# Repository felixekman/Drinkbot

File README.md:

Drinkbot
========

An attempt at controlling a bunch of peristaltic pumps

I have ordered 8 Peristaltic Pumps. 12VDC 200-300mA
  https://www.adafruit.com/products/1150

I hope to drive them via a Raspberry Pi Model B and a Spark core.
I want to be able to control the pumps individually with Mosfets for ON/OFF operation (Possibly via PWM) from the GPIO pins on the Raspberry Pi. I hope to connect the pumps via RJ45 connectors for easy connect and disconnect. I want to drive the entire system from a single 12V power supply.
My current plan is to build my own PCB (first time ever so I need a little help) using these components and ordering the PCB from OSHPark.

Components for the build:

1 pcs Raspberry Pi Model B

1 pcs Spark Core http://spark.io

8 pcs Peristaltic Pumps. 12VDC 200-300mA (https://www.adafruit.com/products/1150)

8 pcs RJ45 8-Pin connectors (https://www.sparkfun.com/products/643)

8 pcs N-Channel MOSFET 60V 30A FQP30N06L (https://www.sparkfun.com/products/10213)

8 pcs 10k Ohm 1/4th W Resistors (https://www.sparkfun.com/products/8374)

8 pcs 1N4007 Diode MIC DO-41 1A 1000V Rectifier Diode

1 pcs Voltage Regulator - 5V L7805 (https://www.sparkfun.com/products/107)

1 pcs Raspberry Pi - GPIO Shrouded Header (2x13)

This project is released under Open Source Hardware (OSHW) licence and the coming software is released under a OSI-approved open source license!

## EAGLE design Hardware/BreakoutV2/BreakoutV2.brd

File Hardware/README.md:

Drinkbot
========

Version 1 of Drinkbot Hardware
Schematics and Layout in Eagle CAD

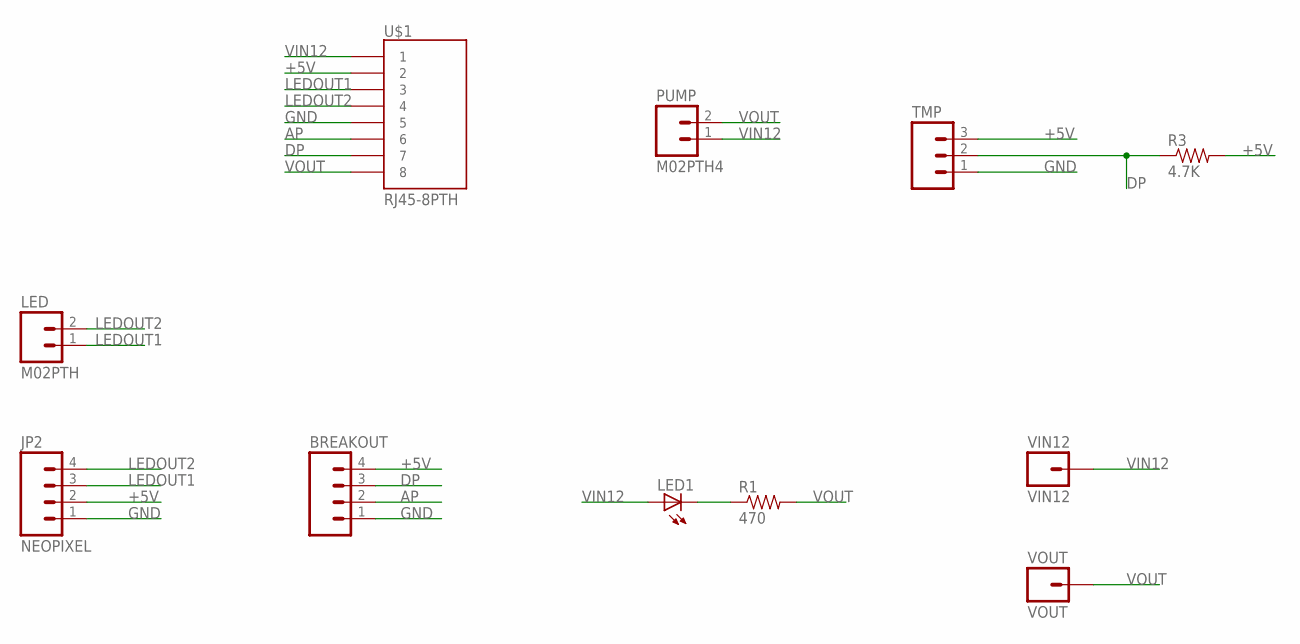
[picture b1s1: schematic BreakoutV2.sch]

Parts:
BREAKOUT: M04PTH; 1X04
JP2: NEOPIXEL; 1X04
LED: M02PTH; 1X02
LED1: LED5MM
PUMP: M02PTH4; 1X02_XTRA_BIG
R1: 470; 1/6W-RES
R3: 4.7K; 1/6W-RES
TMP: M03PTH; 1X03
U$1: RJ45-8PTH; RJ45-8
VIN12: VIN12; 1X01_POGOPIN_HOLE_0.58
VOUT: VOUT; 1X01_POGOPIN_HOLE_0.58

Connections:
+5V: BREAKOUT.4, JP2.2, R3.2, TMP.3, U$1.2
AP: BREAKOUT.2, U$1.6
DP: BREAKOUT.3, R3.1, TMP.2, U$1.7
GND: BREAKOUT.1, JP2.1, TMP.1, U$1.5
LEDOUT1: JP2.3, LED.1, U$1.3
LEDOUT2: JP2.4, LED.2, U$1.4
unnamed: LED1.K (C), R1.1
VIN12: LED1.A, PUMP.1, U$1.1, VIN12.1
VOUT: PUMP.2, R1.2, U$1.8, VOUT.1

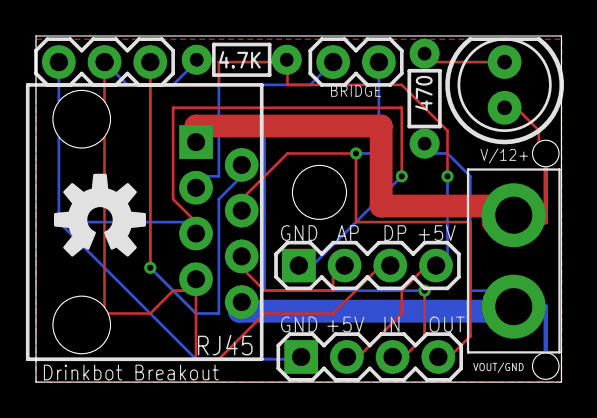
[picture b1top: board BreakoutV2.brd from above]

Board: 2 copper layers, 29.2 x 19.2 mm, 12 parts (0 on the bottom side), 9 nets.

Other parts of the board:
U$2: OSHW-LOGO-M

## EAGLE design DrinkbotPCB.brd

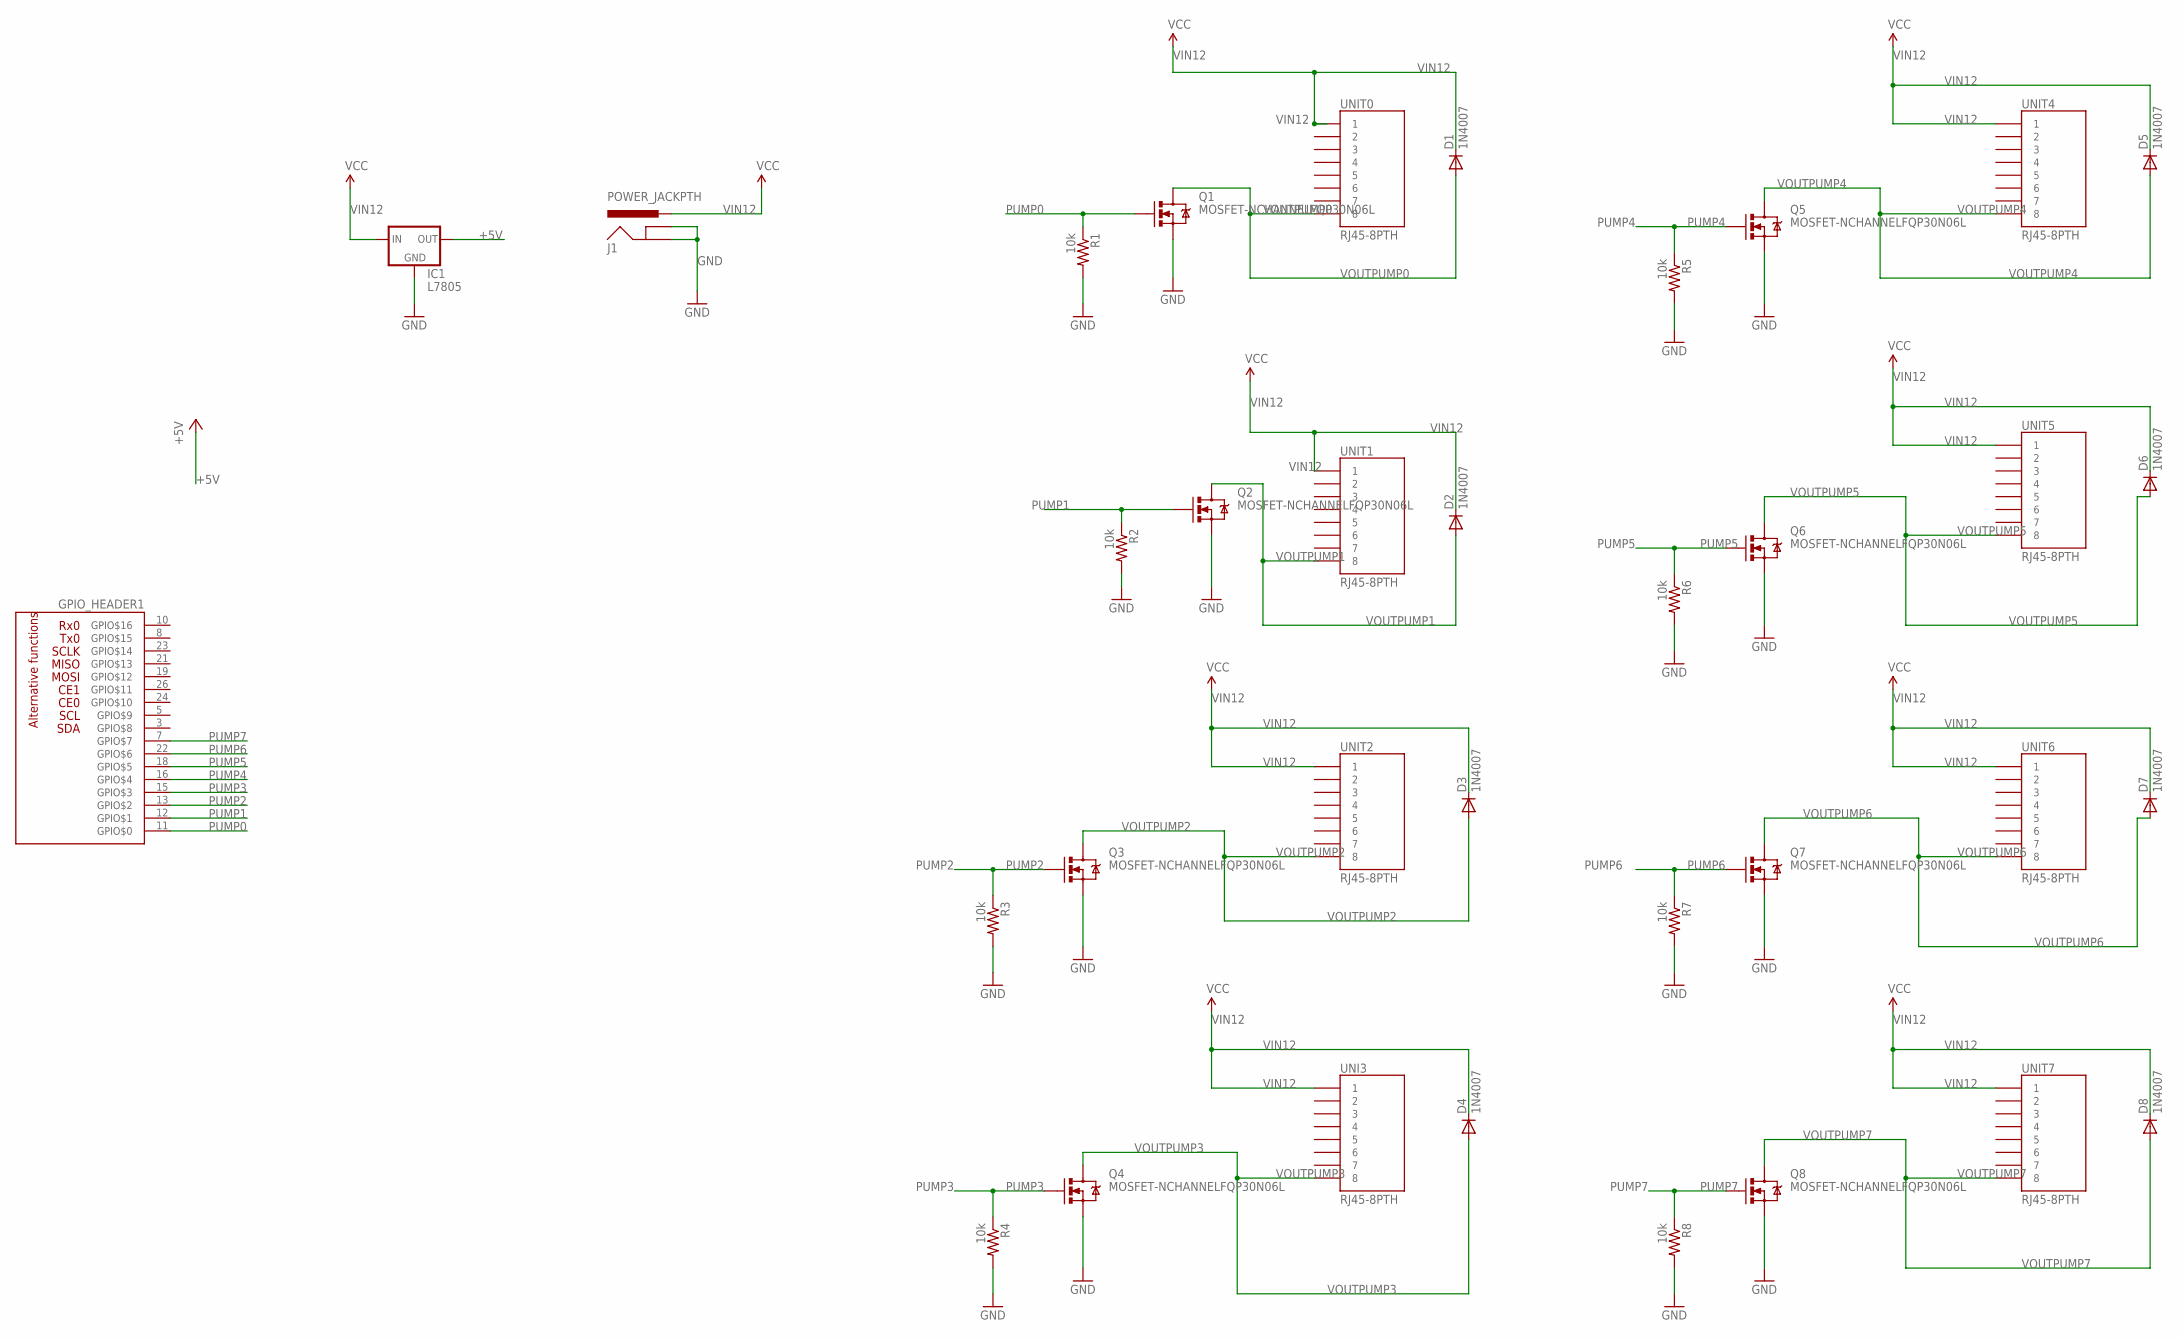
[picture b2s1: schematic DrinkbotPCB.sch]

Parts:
D1, D2, D3, D4, D5, D6, D7, D8: 1N4007; DIODE-1N4001
GPIO_HEADER1: RPI_GPIO_HEADER; 2X13
IC1: L7805; TO220-IGO
J1: POWER_JACKPTH; POWER_JACK_PTH
Q1, Q2, Q3, Q4, Q5, Q6, Q7, Q8: MOSFET-NCHANNELFQP30N06L; TO220V
R1, R2, R3, R4, R5, R6, R7, R8: 10k; AXIAL-0.4
UNI3: RJ45-8PTH; RJ45-8
UNIT0, UNIT1, UNIT2, UNIT4, UNIT5, UNIT6, UNIT7: RJ45-8PTH; RJ45-8

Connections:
+3V3: GPIO_HEADER1.1 (+3V3), GPIO_HEADER1.17 (+3V3)
+5V: GPIO_HEADER1.2 (+5V), GPIO_HEADER1.4 (+5V), IC1.OUT
GND: GPIO_HEADER1.6 (GND), GPIO_HEADER1.9 (GND), GPIO_HEADER1.14 (GND), GPIO_HEADER1.20 (GND), GPIO_HEADER1.25 (GND), IC1.GND, J1.GND, J1.GNDBREAK, Q1.3 (S), Q2.3 (S), Q3.3 (S), Q4.3 (S), Q5.3 (S), Q6.3 (S), Q7.3 (S), Q8.3 (S), R1.P$2 (2), R2.P$2 (2), R3.P$2 (2), R4.P$2 (2), R5.P$2 (2), R6.P$2 (2), R7.P$2 (2), R8.P$2 (2)
PUMP0: GPIO_HEADER1.11 (GPIO$0), Q1.1 (G), R1.P$1 (1)
PUMP1: GPIO_HEADER1.12 (GPIO$1), Q2.1 (G), R2.P$1 (1)
PUMP2: GPIO_HEADER1.13 (GPIO$2), Q3.1 (G), R3.P$1 (1)
PUMP3: GPIO_HEADER1.15 (GPIO$3), Q4.1 (G), R4.P$1 (1)
PUMP4: GPIO_HEADER1.16 (GPIO$4), Q5.1 (G), R5.P$1 (1)
PUMP5: GPIO_HEADER1.18 (GPIO$5), Q6.1 (G), R6.P$1 (1)
PUMP6: GPIO_HEADER1.22 (GPIO$6), Q7.1 (G), R7.P$1 (1)
PUMP7: GPIO_HEADER1.7 (GPIO$7), Q8.1 (G), R8.P$1 (1)
VIN12: D1.C, D2.C, D3.C, D4.C, D5.C, D6.C, D7.C, D8.C, IC1.IN, J1.PWR, UNI3.1, UNIT0.1, UNIT1.1, UNIT2.1, UNIT4.1, UNIT5.1, UNIT6.1, UNIT7.1
VOUTPUMP0: D1.A, Q1.2 (D), UNIT0.8
VOUTPUMP1: D2.A, Q2.2 (D), UNIT1.8
VOUTPUMP2: D3.A, Q3.2 (D), UNIT2.8
VOUTPUMP3: D4.A, Q4.2 (D), UNI3.8
VOUTPUMP4: D5.A, Q5.2 (D), UNIT4.8
VOUTPUMP5: D6.A, Q6.2 (D), UNIT5.8
VOUTPUMP6: D7.A, Q7.2 (D), UNIT6.8
VOUTPUMP7: D8.A, Q8.2 (D), UNIT7.8

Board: 2 copper layers, 35 parts (0 on the bottom side), 20 nets, no tracks yet.

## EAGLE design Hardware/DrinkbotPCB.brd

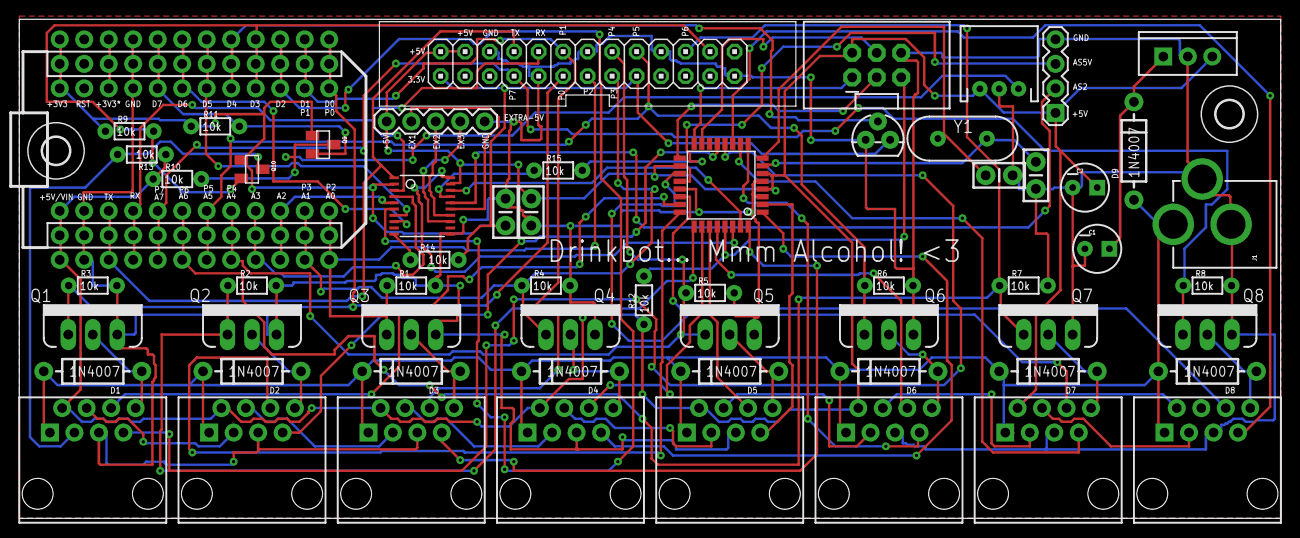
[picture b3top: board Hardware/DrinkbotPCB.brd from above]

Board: 2 copper layers, 130.8 x 51.7 mm, 62 parts (0 on the bottom side), 72 nets.

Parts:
C1, C2: 10uF; CPOL-RADIAL-10UF-25V
C3, C4: 22pf; CAP-PTH-SMALL-KIT
C5, C6: 0.1uF; CAP-PTH-SMALL-KIT
D1, D2, D3, D4, D5, D6, D7, D8, D9: 1N4007; DIODE-1N4001
EXTRA-5V: 1X05
GPIO_HEADER1: RPI-GPIO; 2X13
IC1: L7805-5V; TO220-IGO
J1: 12V-PWR; POWER_JACK_PTH
JP1: RGBLED1; JST-3-PTH
JP3: ISP; 2X3-SHROUDED
JP4: ALCOHOL; 1X04
Q1, Q2, Q3, Q4, Q5, Q6, Q7, Q8: FQP30N06L; TO220V
Q9, Q10: BSS138; SOT23
R1, R2, R3, R4, R5, R6, R7, R8, R9, R10, R11, R12, R13, R14, R15: 10k; 1/6W-RES
U1: ATMEGA328P; TQFP32-08
U2: TXB0108; TSSOP20
U$1: SPARK-CORE; SPARK_CORE_STACKABLE
U$2: TMP; TO-92
U$3, U$7: 2,8
UNI3: RJ45-8PTH; RJ45-8
UNIT0, UNIT1, UNIT2, UNIT4, UNIT5, UNIT6, UNIT7: RJ45-8PTH; RJ45-8
Y1: 16Mhz; HC49US

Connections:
+3V3: C6.1, GPIO_HEADER1.1, GPIO_HEADER1.17, Q9.1, Q10.1, R9.1, R11.1, R14.1, U2.2, U$1.24, U$1.#24, U$1.@24, U$2.3
+5V: C2.1, C5.1, EXTRA-5V.5, GPIO_HEADER1.2, GPIO_HEADER1.4, IC1.OUT, JP1.1, JP3.2, JP4.1, R10.1, R12.1, R13.1, U1.4, U1.6, U1.18, U1.20, U2.19, U$1.1, U$1.#1, U$1.@1, UNI3.2, UNIT0.2, UNIT1.2, UNIT2.2, UNIT4.2, UNIT5.2, UNIT6.2, UNIT7.2
AP0: U1.23, UNIT0.6
AP1: U1.24, UNIT1.6
AP2: U1.25, UNIT2.6
AP3: U1.26, UNI3.6
AP4: U1.27, UNIT4.6
AP5: U1.28, UNIT5.6
AP6: U1.19, UNIT6.6
AP7: U1.22, UNIT7.6
AS2-3V: U2.5, U$1.10, U$1.#10, U$1.@10
AS2-5V: JP4.2, U2.16
AS3V: U2.4, U$1.9, U$1.#9, U$1.@9
AS5V: R15.1, U2.17
AT-RX: U1.30, U2.20
AT-TX: U1.31, U2.18
DP0: U1.12, UNIT0.7
DP1: U1.13, UNIT1.7
DP2: U1.32, UNIT2.7
DP3: U1.1, UNI3.7
DP4: U1.2, UNIT4.7
DP5: U1.9, UNIT5.7
DP6: U1.10, UNIT6.7
DP7: U1.11, UNIT7.7
EXTRA1-3V3: U2.6, U$1.15, U$1.#15, U$1.@15
EXTRA1-5V: EXTRA-5V.4, U2.15
EXTRA2-3V3: U2.7, U$1.18, U$1.#18, U$1.@18
EXTRA2-5V: EXTRA-5V.3, U2.14
EXTRA3-3V3: U2.8, U$1.19, U$1.#19, U$1.@19
EXTRA3-5V: EXTRA-5V.2, U2.13
GND: C1.2, C2.2, C3.1, C4.1, C5.2, C6.2, EXTRA-5V.1, GPIO_HEADER1.6, GPIO_HEADER1.9, GPIO_HEADER1.14, GPIO_HEADER1.20, GPIO_HEADER1.25, IC1.GND, J1.GND, J1.GNDBREAK, JP1.2, JP3.6, JP4.4, Q1.3, Q2.3, Q3.3, Q4.3, Q5.3, Q6.3, Q7.3, Q8.3, R1.2, R2.2, R3.2, R4.2, R5.2, R6.2, R7.2, R8.2, U1.3, U1.5, U1.21, U2.11, U$1.2, U$1.21, U$1.#2, U$1.#21, U$1.@2, U$1.@21, U$2.1, UNI3.5, UNIT0.5, UNIT1.5, UNIT2.5, UNIT4.5, UNIT5.5, UNIT6.5, UNIT7.5
HV1: JP1.3, Q9.3, R10.2
LEDIN0: Q10.3, R13.2, UNIT0.3
LEDOUT0: UNIT0.4, UNIT1.3
LEDOUT1: UNIT1.4, UNIT2.3
LEDOUT2: UNI3.3, UNIT2.4
LEDOUT3: UNI3.4, UNIT4.3
LEDOUT4: UNIT4.4, UNIT5.3
LEDOUT5: UNIT5.4, UNIT6.3
LEDOUT6: UNIT6.4, UNIT7.3
LV-RX: GPIO_HEADER1.10, U2.3, U$1.4, U$1.#4, U$1.@4
LV-TX: GPIO_HEADER1.8, U2.1, U$1.3, U$1.#3, U$1.@3
MISO: JP3.1, U1.16
MOSI: JP3.4, U1.15
unnamed: C1.1, D9.C, IC1.IN
unnamed: C3.2, U1.7, Y1.2
unnamed: C4.2, U1.8, Y1.1
unnamed: R14.2, U2.10
unnamed: JP4.3, R15.2
PUMP0: GPIO_HEADER1.11, Q1.1, R3.1, U$1.13, U$1.#13, U$1.@13
PUMP1: GPIO_HEADER1.12, Q2.1, R2.1, U$1.14, U$1.#14, U$1.@14
PUMP2: GPIO_HEADER1.13, Q3.1, R1.1, U$1.12, U$1.#12, U$1.@12
PUMP3: GPIO_HEADER1.15, Q4.1, R4.1, U$1.11, U$1.#11, U$1.@11
PUMP4: GPIO_HEADER1.16, Q5.1, R5.1, U$1.8, U$1.#8, U$1.@8
PUMP5: GPIO_HEADER1.18, Q6.1, R6.1, U$1.7, U$1.#7, U$1.@7
PUMP6: GPIO_HEADER1.22, Q7.1, R7.1, U$1.6, U$1.#6, U$1.@6
PUMP7: GPIO_HEADER1.7, Q8.1, R8.1, U$1.5, U$1.#5, U$1.@5
PUMPLEDS: GPIO_HEADER1.24, Q10.2, R9.2, U$1.16, U$1.#16, U$1.@16
RESET: JP3.5, R12.2, U1.29
RGBLED1: Q9.2, R11.2, U$1.20, U$1.#20, U$1.@20
SCK: JP3.3, U1.17
TEMPSENSOR1: U$1.17, U$1.#17, U$1.@17, U$2.2
VDDA: U$1.22, U$1.#22, U$1.@22
VIN12: D1.C, D2.C, D3.C, D4.C, D5.C, D6.C, D7.C, D8.C, D9.A, J1.PWR, UNI3.1, UNIT0.1, UNIT1.1, UNIT2.1, UNIT4.1, UNIT5.1, UNIT6.1, UNIT7.1
VOUTPUMP0: D1.A, Q1.2, UNIT0.8
VOUTPUMP1: D2.A, Q2.2, UNIT1.8
VOUTPUMP2: D3.A, Q3.2, UNIT2.8
VOUTPUMP3: D4.A, Q4.2, UNI3.8
VOUTPUMP4: D5.A, Q5.2, UNIT4.8
VOUTPUMP5: D6.A, Q6.2, UNIT5.8
VOUTPUMP6: D7.A, Q7.2, UNIT6.8
VOUTPUMP7: D8.A, Q8.2, UNIT7.8

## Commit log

2014-11-29 Initial upload of PCB/Schematics
2014-11-29 PDF Schematics
2014-12-01 Updated Schematics/Gerbers/Board Layout
2014-12-17 Updated PDF
2014-12-20 Added New Information
2014-12-20 FlowChart added
2014-12-21 Added some Graphics and GUI Ideas
2014-12-21 Structure
2014-12-25 Added Breakout Board
2014-12-27 Added Drink Icons
2014-12-27 New Logo & Rev. 2 for Drink Icons
    Reason: Calle…
2014-12-27 Updated Logo
2014-12-27 New Revised GUI and Templates
2014-12-27 Updated Graphics
2014-12-27 AppGUI Updated
2014-12-28 App Development is added
2014-12-28 Sample Database
2015-01-02 Proper license text added
2015-01-03 Initial Code from librae8226
    Our first initial code from the wonderful librae8226
2015-01-03 Dev Code
2015-01-03 RGB Function added
2015-01-04 Updated Dev Code
2015-01-04 Updated RGB Strip Support
    The code now shows on rub led strip which pump is active. Also when
    pumping is done, an animation is shown to signal the drink is ready.
2015-01-09 Updated Code
    Updated code curtesy of Librae8226
    Also new RGB Led code from Felix
    1. refine code, remove unused code
    2. support dallas temperature sensor (onewire)
    3. support mq3 alcohol sensor
    4. work around virtual com port hang issue
2015-01-11 Supports customize each pump for its performance
    Use the const array millisPerVol[] to store the fixed parameter.
    Also, add a syslog macro for a better debugging purpose.
    Changes made by Librae8226
2016-01-02 All Code Available for Public (Project Dormant)
    All Code Available for Public under license (Project is Dormant)
2016-01-02 Updated Structure

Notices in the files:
Hardware/DrinkbotPCB.brd:
Copyright 2015
parts and their libraries:
SparkFun-Connectors: Licensing: CC v3.0 Share-Alike You are welcome to use this library for commercial purposes.
